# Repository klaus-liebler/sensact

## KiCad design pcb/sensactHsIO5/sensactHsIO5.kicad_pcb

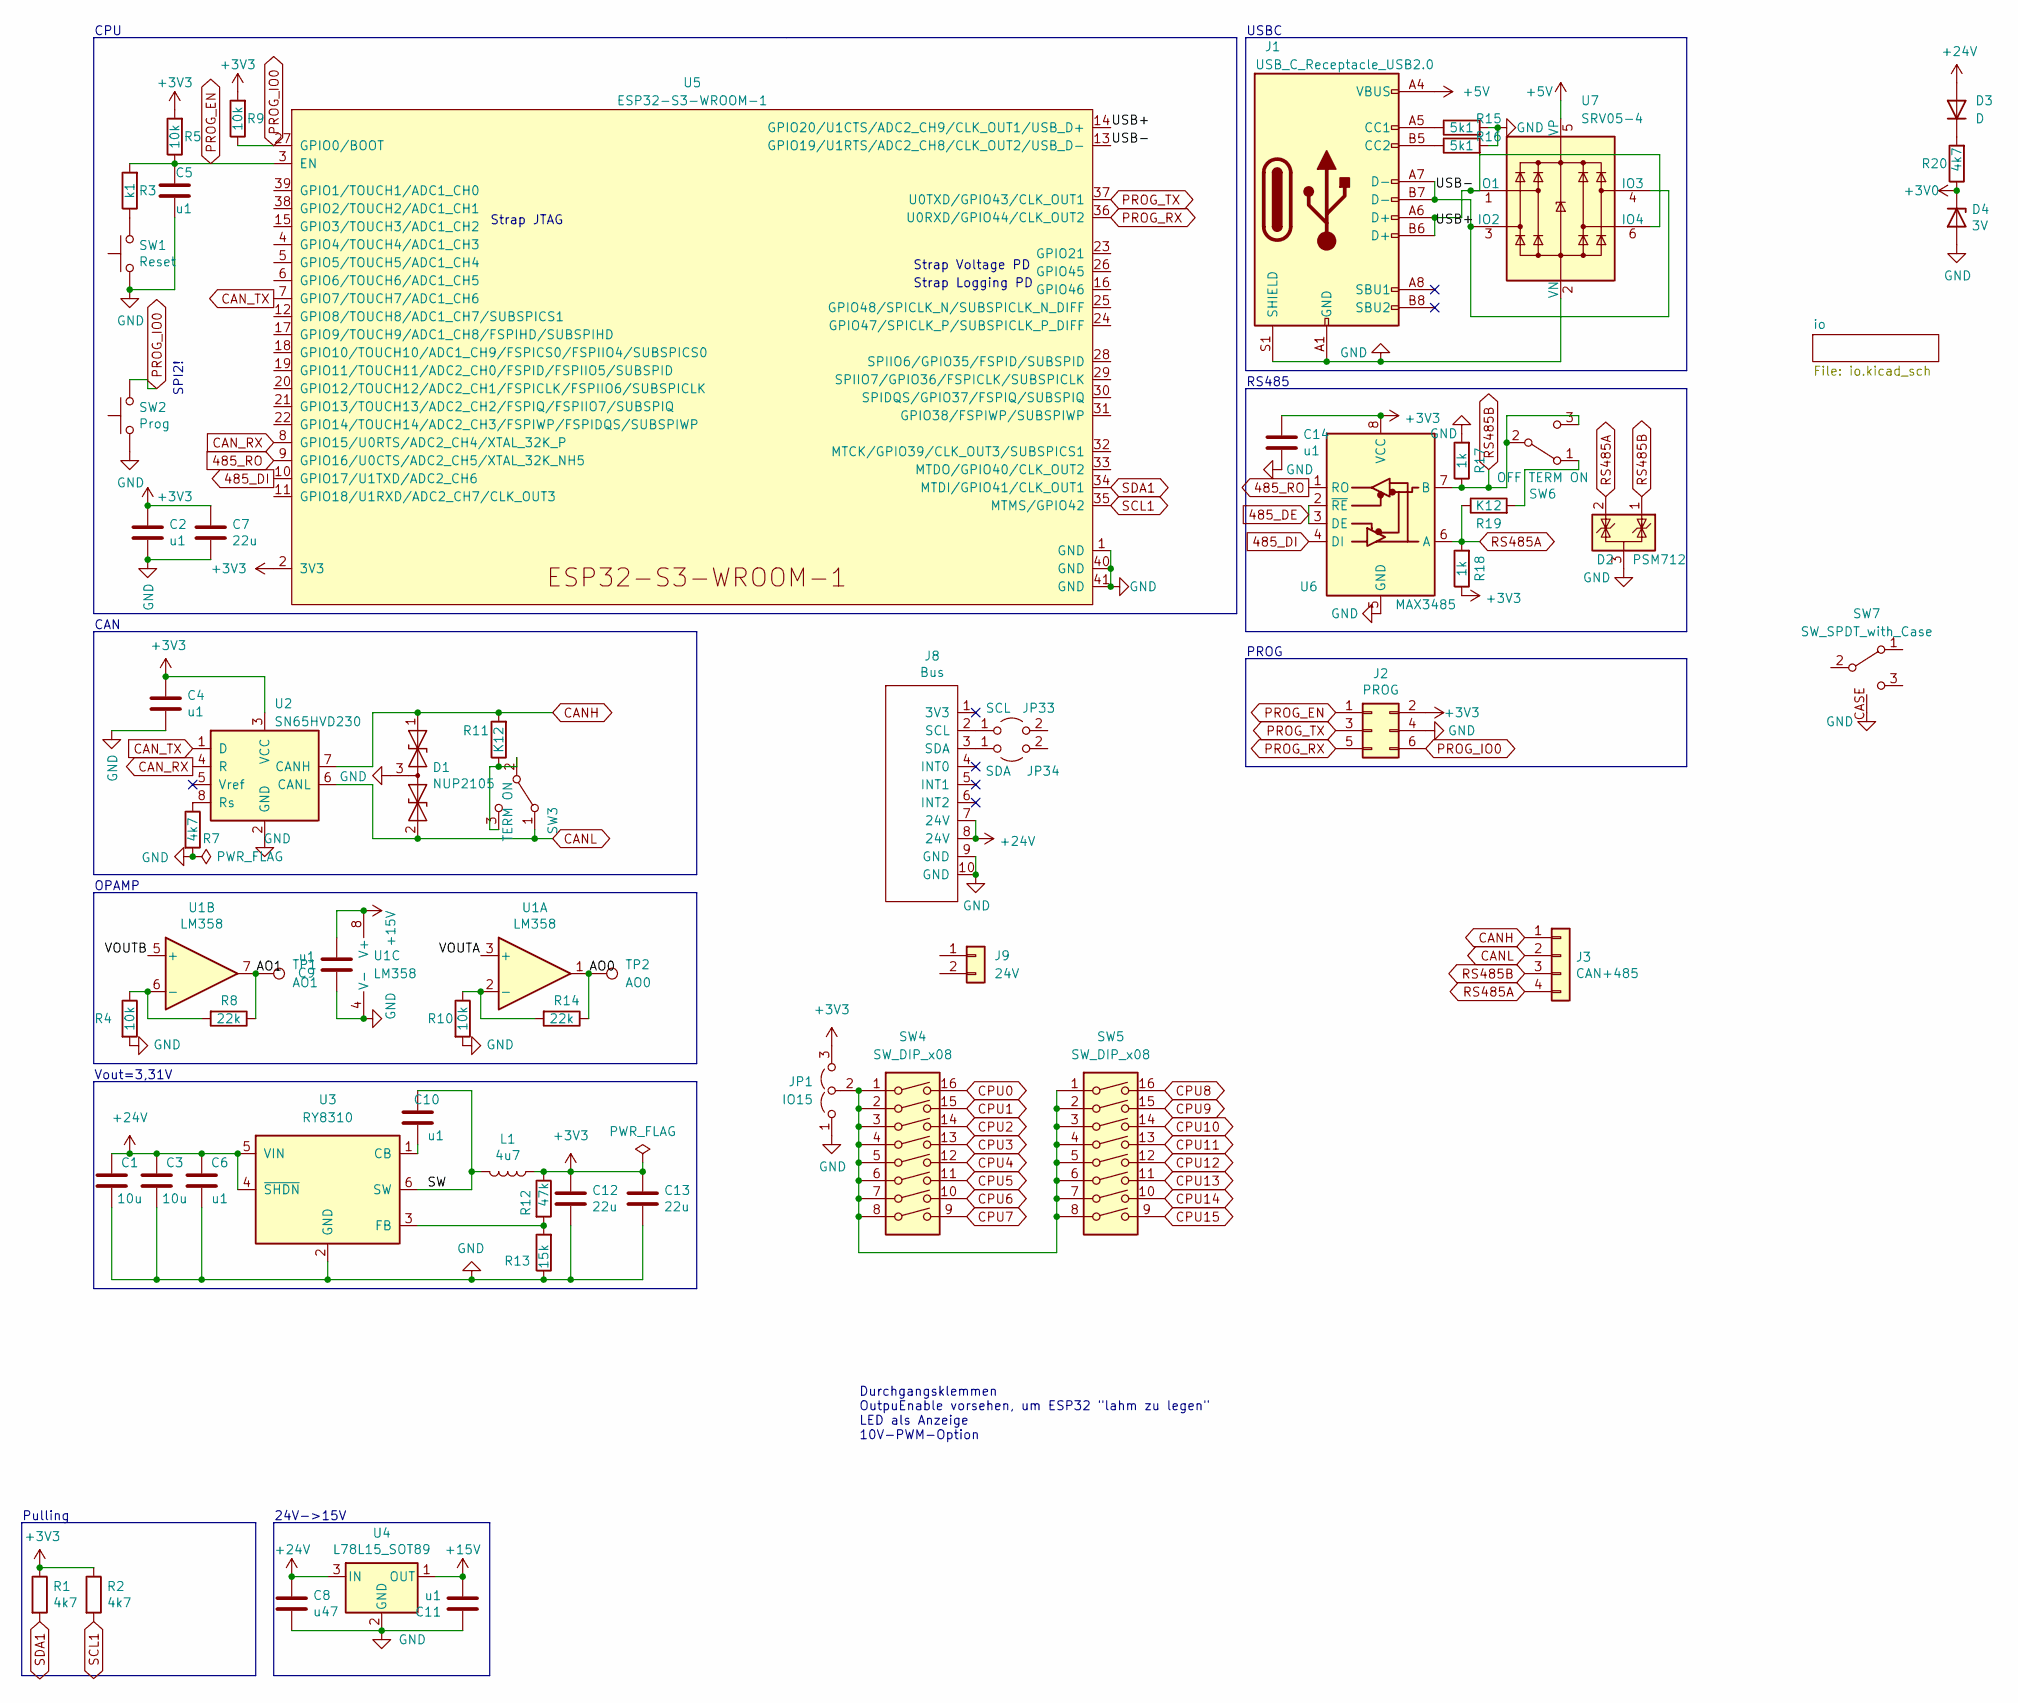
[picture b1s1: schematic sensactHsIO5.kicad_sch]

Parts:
C1, C3: 10u; C_1206_3216Metric
C2, C4, C5, C9, C11, C14: u1; C_0402_1005Metric
C6, C10: u1; C_0603_1608Metric
C7, C12, C13: 22u; C_0603_1608Metric
C8: u47; C_0805_2012Metric
D1: NUP2105; SOT-23_Handsoldering
D2: PSM712; SOT-23_Handsoldering
D3: D; D_SOD-123
D4: 3V; D_SOD-123
J1: USB_C_Receptacle_USB2.0; USB_C_Receptacle_HRO_TYPE-C-31-M-12_smaller
J2: PROG; IDC_2x03_P1.27mm_Vertical
J3: CAN+485; PhoenixContact_MC_1,5_4-G-3.5_1x04_P3.50mm_Horizontal_small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
J8: Bus; IDC-Header_2x05_P2.54mm_Horizontal_tightCrtYd
J9: 24V; PhoenixContact_MC_1,5_2-G-3.5_1x02_P3.50mm_Horizontal
JP1: IO15; SolderJumper-3_P1.3mm_Open_RoundedPad1.0x1.5mm_smaller
JP33: SCL; SolderJumper-2_P1.3mm_Bridged2Bar_RoundedPad1.0x1.5mm
JP34: SDA; SolderJumper-2_P1.3mm_Bridged2Bar_RoundedPad1.0x1.5mm
L1: 4u7; L_Abracon_ASPI-0630LR
R1, R2, R7: 4k7; R_0402_1005Metric
R3: k1; R_0402_1005Metric
R4, R5, R9, R10: 10k; R_0402_1005Metric
R8, R14: 22k; R_0402_1005Metric
R11, R19: K12; R_1206_3216Metric_Pad1.30x1.75mm_HandSolder
R12: 47k; R_0402_1005Metric
R13: 15k; R_0402_1005Metric
R15, R16: 5k1; R_0402_1005Metric
R17, R18: 1k; R_0603_1608Metric
R20: 4k7; R_1206_3216Metric
SW1: Reset; Button_2x4x3,5_handsolder
SW2: Prog; Button_2x4x3,5_handsolder
SW3: TERM ON; SW_SPDT_PCM12_handsolder
SW4, SW5: SW_DIP_x08; SW_DIP_SPSTx08_Piano
SW6: OFF TERM ON; SW_SPDT_PCM12_handsolder
SW7: SW_SPDT_with_Case; SW_SPDT_PCM12_handsolder
TP1: AO1; TestPoint_Pad_2.0x2.0mm
TP2: AO0; TestPoint_Pad_2.0x2.0mm
U1: LM358; SOIC-8_3.9x4.9mm_P1.27mm
U2: SN65HVD230; SOIC-8_3.9x4.9mm_P1.27mm
U3: RY8310; SOT-23-6
U4: L78L15_SOT89; SOT-89-3_Handsoldering
U5: ESP32-S3-WROOM-1; ESP32-S3-WROOM-1U
U6: MAX3485; SOIC-8_3.9x4.9mm_P1.27mm
U7: SRV05-4; SOT-23-6

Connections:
485_DE: U6.2 (~RE), U6.3 (DE)
485_DI: U5.10 (GPIO17/U1TXD/ADC2_CH6), U6.4 (DI)
485_RO: U5.9 (GPIO16/U0CTS/ADC2_CH5/XTAL_32K_NH5), U6.1 (RO)
+3V0: D4.1 (K), R20.1; also elsewhere on the board
+3V3: C2.1, C4.1, C7.1, C12.1, C13.1, C14.2, J2.2, JP1.3 (B), L1.1, R1.1, R2.1, R5.2, R9.2, R12.1, R18.1, U2.3 (VCC), U5.2 (3V3), U6.8 (VCC); also elsewhere on the board
+5V: J1.A4 (VBUS), J1.A9 (VBUS), J1.B4 (VBUS), J1.B9 (VBUS), U7.5 (VP)
+15V: C9.2, C11.2, U1.8 (V+), U4.1 (OUT)
+24V: C1.2, C3.2, C6.2, C8.1, D3.2 (A), J8.7 (24V), J8.8 (24V), U3.4 (~SHDN), U3.5 (VIN), U4.3 (IN); also elsewhere on the board
/AO0: R14.1, TP2.1, U1.1
/AO1: R8.1, TP1.1, U1.7
/SW: C10.2, L1.2, U3.6 (SW)
/USB+: J1.A6 (D+), J1.B6 (D+), U5.14 (GPIO20/U1CTS/ADC2_CH9/CLK_OUT1/USB_D+), U7.1 (IO1), U7.6 (IO4)
/USB-: J1.A7 (D-), J1.B7 (D-), U5.13 (GPIO19/U1RTS/ADC2_CH8/CLK_OUT2/USB_D-), U7.3 (IO2), U7.4 (IO3)
/VOUTA: U1.3 (+)
/VOUTB: U1.5 (+)
CANH: D1.1 (A1), J3.1, R11.2, U2.7 (CANH)
CANL: D1.2 (A2), J3.2, SW3.1 (A), U2.6 (CANL)
CAN_RX: U2.4 (R), U5.8 (GPIO15/U0RTS/ADC2_CH4/XTAL_32K_P)
CAN_TX: U2.1 (D), U5.7 (GPIO7/TOUCH7/ADC1_CH6)
CPU0: SW4.16; also elsewhere on the board
CPU1: SW4.15; also elsewhere on the board
CPU2: SW4.14; also elsewhere on the board
CPU3: SW4.13; also elsewhere on the board
CPU4: SW4.12; also elsewhere on the board
CPU5: SW4.11; also elsewhere on the board
CPU6: SW4.10; also elsewhere on the board
CPU7: SW4.9; also elsewhere on the board
CPU8: SW5.16; also elsewhere on the board
CPU9: SW5.15; also elsewhere on the board
CPU10: SW5.14; also elsewhere on the board
CPU11: SW5.13; also elsewhere on the board
CPU12: SW5.12; also elsewhere on the board
CPU13: SW5.11; also elsewhere on the board
CPU14: SW5.10; also elsewhere on the board
CPU15: SW5.9; also elsewhere on the board
GND: C1.1, C2.2, C3.1, C4.2, C5.2, C6.1, C7.2, C8.2, C9.1, C11.1, C12.2, C13.2, C14.1, D1.3 (common), D2.3 (A), D4.2 (A), J1.A1 (GND), J1.A12 (GND), J1.B1 (GND), J1.B12 (GND), J1.S1 (SHIELD), J2.4, J8.9 (GND), J8.10 (GND), JP1.1 (A), R4.2, R7.2, R10.2, R13.1, R15.2, R16.2, R17.2, SW1.1, SW2.1, SW7.CASE, U1.4 (V-), U2.2 (GND), U3.2 (GND), U4.2 (GND), U5.1 (GND), U5.40 (GND), U5.41 (GND), U6.5 (GND), U7.2 (VN); also elsewhere on the board
unnamed: C10.1, U3.1 (CB)
unnamed: D3.1 (K), R20.2
unnamed: J1.A5 (CC1), R15.1
unnamed: J1.B5 (CC2), R16.1
unnamed: J8.2 (SCL), JP33.1 (A)
unnamed: J8.3 (SDA), JP34.1 (A)
unnamed: JP1.2 (C), SW4.1, SW4.2, SW4.3, SW4.4, SW4.5, SW4.6, SW4.7, SW4.8, SW5.1, SW5.2, SW5.3, SW5.4, SW5.5, SW5.6, SW5.7, SW5.8
unnamed: R3.1, SW1.2
unnamed: R4.1, R8.2, U1.6 (-)
unnamed: R7.1, U2.8 (Rs)
unnamed: R10.1, R14.2, U1.2 (-)
unnamed: R12.2, R13.2, U3.3 (FB)
unnamed: R19.2, SW6.1 (A)
unnamed: R11.1, SW3.2 (B), SW3.3 (C)
PROG_EN: C5.1, J2.1, R3.2, R5.1, U5.3 (EN)
PROG_IO0: J2.6, R9.1, SW2.2, U5.27 (GPIO0/BOOT)
PROG_RX: J2.5, U5.36 (U0RXD/GPIO44/CLK_OUT2)
PROG_TX: J2.3, U5.37 (U0TXD/GPIO43/CLK_OUT1)
RS485A: D2.2 (K), J3.4, R18.2, R19.1, U6.6 (A)
RS485B: D2.1 (K), J3.3, R17.1, SW6.2 (B), SW6.3 (C), U6.7 (B)
SCL1: R2.2, U5.35 (MTMS/GPIO42)
SDA1: R1.2, U5.34 (MTDI/GPIO41/CLK_OUT1)

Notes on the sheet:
SPI2!
USBC
Strap JTAG
Vout=3,31V
Strap Logging PD
Pulling
PROG
RS485
Durchgangsklemmen OutpuEnable vorsehen, um ESP32 "lahm zu legen" LED als Anzeige 10V-PWM-Option
Strap Voltage PD
OPAMP
CAN
24V->15V
CPU

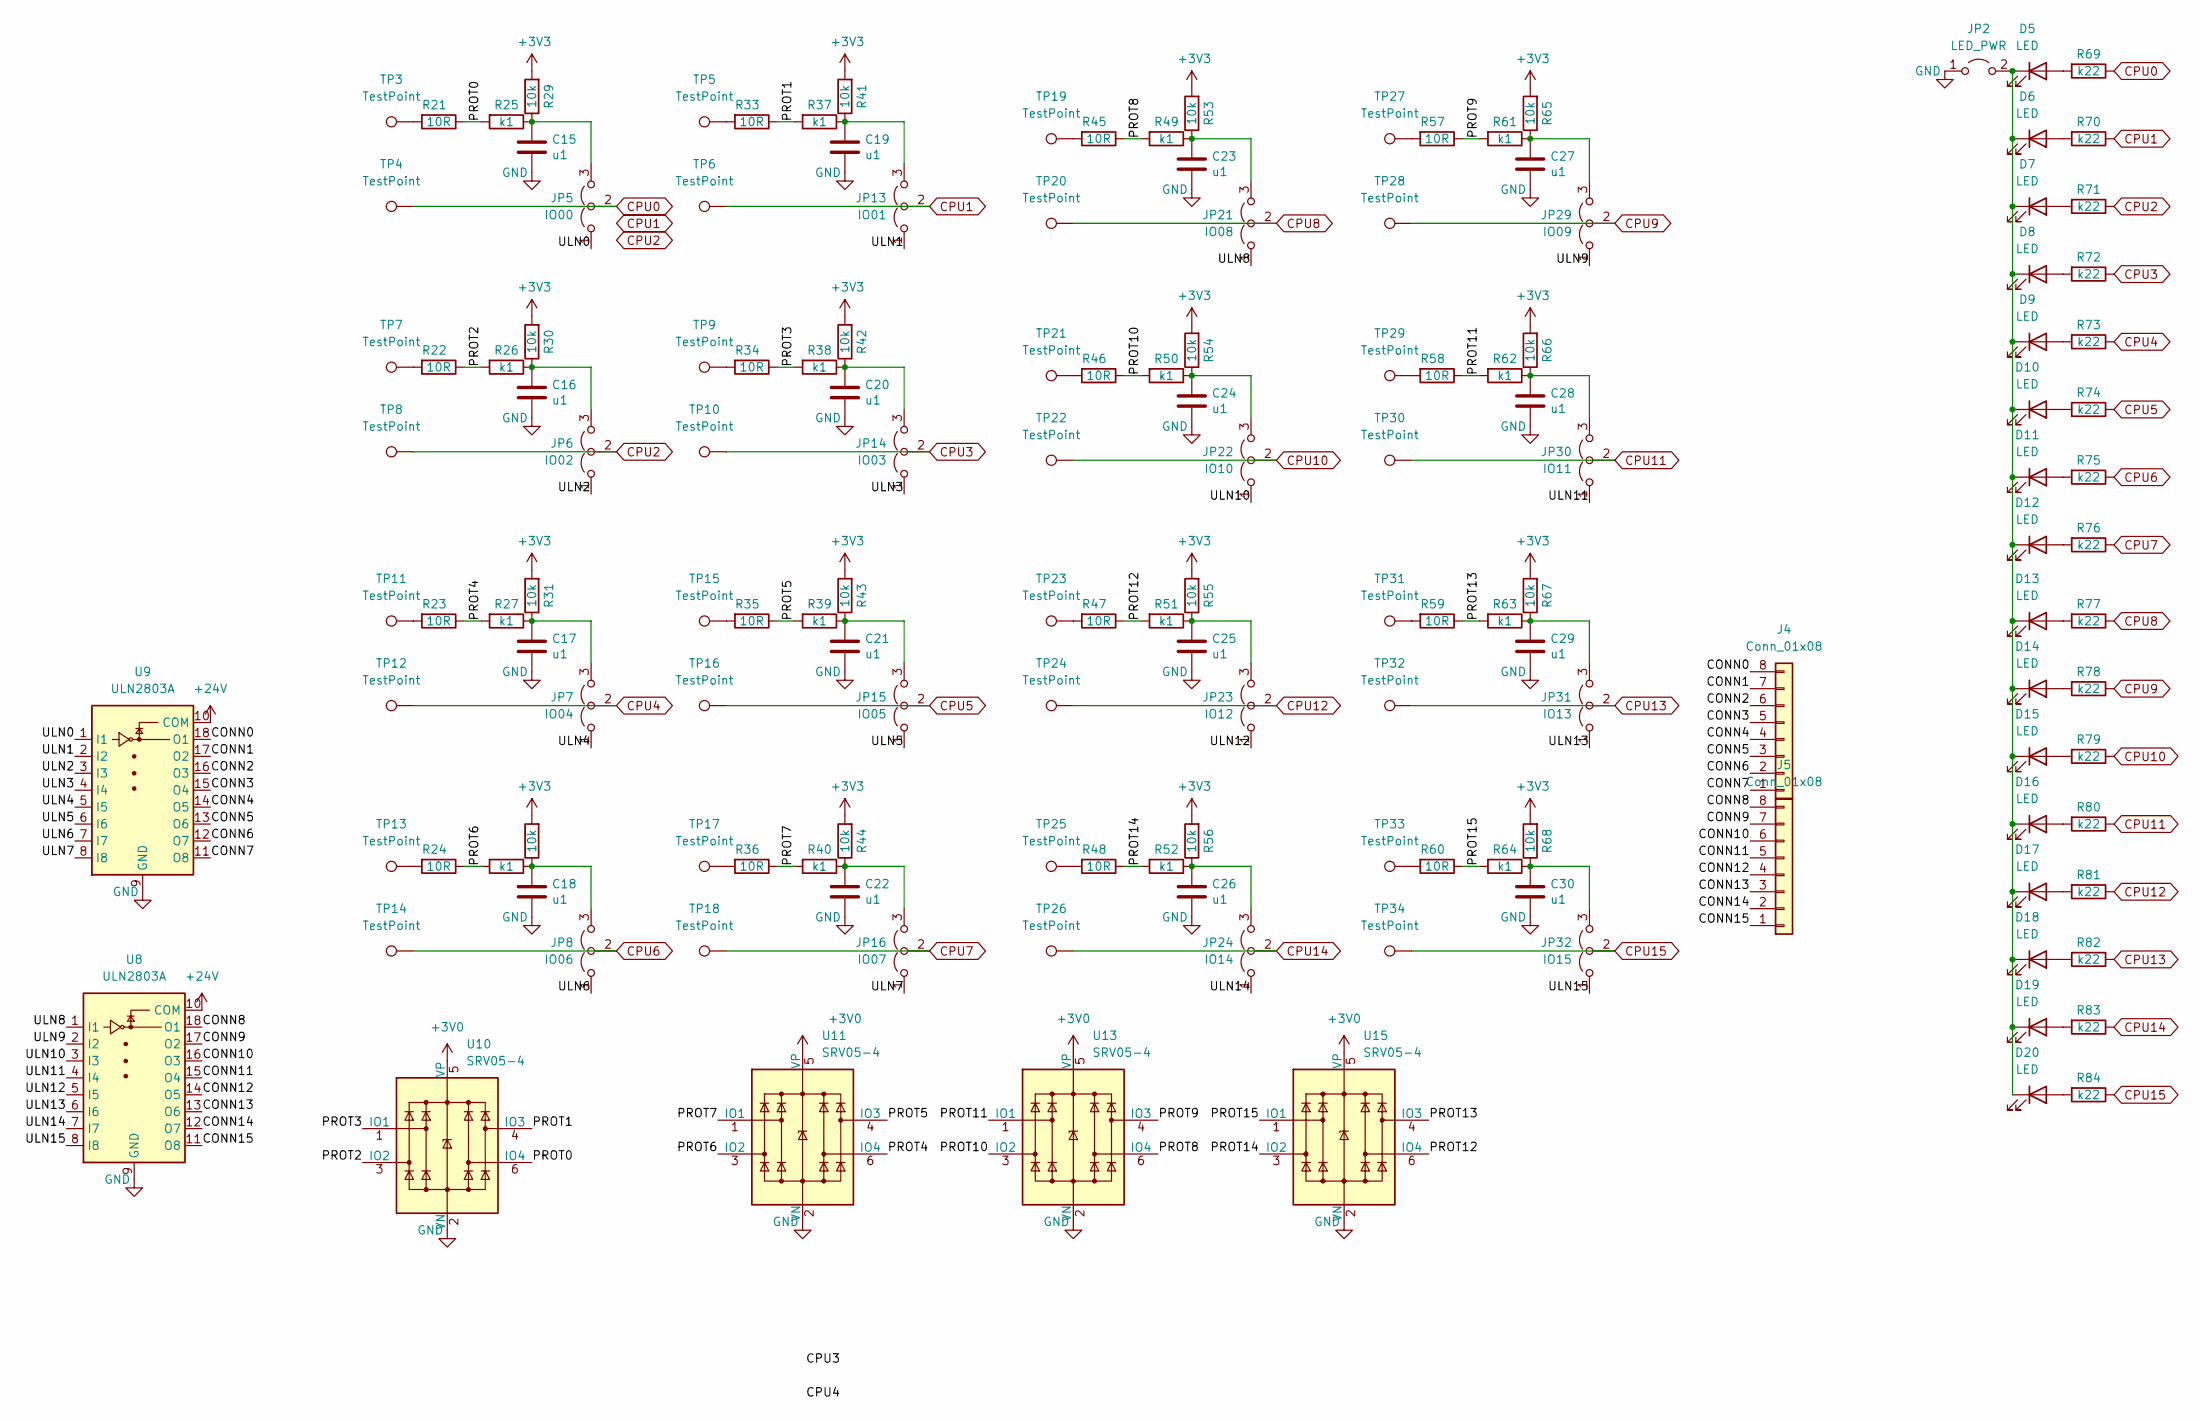
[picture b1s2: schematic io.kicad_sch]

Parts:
C15, C16, C17, C18, C19, C20, C21, C22, C23, C24, C25, C26, C27, C28, C29, C30: u1; C_0402_1005Metric
D5, D6, D7, D8, D9, D10, D11, D12, D13, D14, D15, D16, D17, D18, D19, D20: LED; LED_1606
J4, J5: Conn_01x08; KF141R-8p
JP2: LED_PWR; SolderJumper-2_P1.3mm_Open_RoundedPad1.0x1.5mm
JP5: IO00; SolderJumper-3_P1.3mm_Open_RoundedPad1.0x1.5mm_smaller
JP6: IO02; SolderJumper-3_P1.3mm_Open_RoundedPad1.0x1.5mm_smaller
JP7: IO04; SolderJumper-3_P1.3mm_Open_RoundedPad1.0x1.5mm_smaller
JP8: IO06; SolderJumper-3_P1.3mm_Open_RoundedPad1.0x1.5mm_smaller
JP13: IO01; SolderJumper-3_P1.3mm_Open_RoundedPad1.0x1.5mm_smaller
JP14: IO03; SolderJumper-3_P1.3mm_Open_RoundedPad1.0x1.5mm_smaller
JP15: IO05; SolderJumper-3_P1.3mm_Open_RoundedPad1.0x1.5mm_smaller
JP16: IO07; SolderJumper-3_P1.3mm_Open_RoundedPad1.0x1.5mm_smaller
JP21: IO08; SolderJumper-3_P1.3mm_Open_RoundedPad1.0x1.5mm_smaller
JP22: IO10; SolderJumper-3_P1.3mm_Open_RoundedPad1.0x1.5mm_smaller
JP23: IO12; SolderJumper-3_P1.3mm_Open_RoundedPad1.0x1.5mm_smaller
JP24: IO14; SolderJumper-3_P1.3mm_Open_RoundedPad1.0x1.5mm_smaller
JP29: IO09; SolderJumper-3_P1.3mm_Open_RoundedPad1.0x1.5mm_smaller
JP30: IO11; SolderJumper-3_P1.3mm_Open_RoundedPad1.0x1.5mm_smaller
JP31: IO13; SolderJumper-3_P1.3mm_Open_RoundedPad1.0x1.5mm_smaller
JP32: IO15; SolderJumper-3_P1.3mm_Open_RoundedPad1.0x1.5mm_smaller
R21, R22, R23, R24, R33, R34, R35, R36, R45, R46, R47, R48, R57, R58, R59, R60: 10R; R_0402_1005Metric
R25, R26, R27, R28, R37, R38, R39, R40, R49, R50, R51, R52, R61, R62, R63, R64: k1; R_0402_1005Metric
R29, R30, R31, R32, R41, R42, R43, R44, R53, R54, R55, R56, R65, R66, R67, R68: 10k; R_0402_1005Metric
R69, R70, R71, R72, R73, R74, R75, R76, R77, R78, R79, R80, R81, R82, R83, R84: k22; R_0402_1005Metric
TP3, TP4, TP5, TP6, TP7, TP8, TP9, TP10, TP11, TP12, TP13, TP14, TP15, TP16, TP17, TP18, TP19, TP20, TP21, TP22, TP23, TP24, TP25, TP26, TP27, TP28, TP29, TP30, TP31, TP32, TP33, TP34: TestPoint; SolderJumper-3_forMCConnector
U8, U9: ULN2803A; SOIC-18W_7.5x11.6mm_P1.27mm
U10, U11, U13, U15: SRV05-4; SOT-23-6-spezial

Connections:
+3V0: U10.5 (VP), U11.5 (VP), U13.5 (VP), U15.5 (VP); also elsewhere on the board
+3V3: R29.2, R30.2, R31.2, R32.2, R41.2, R42.2, R43.2, R44.2, R53.2, R54.2, R55.2, R56.2, R65.2, R66.2, R67.2, R68.2; also elsewhere on the board
+24V: U8.10 (COM), U9.10 (COM); also elsewhere on the board
/io/CONN0: J4.8, U9.18 (O1)
/io/CONN1: J4.7, U9.17 (O2)
/io/CONN2: J4.6, U9.16 (O3)
/io/CONN3: J4.5, U9.15 (O4)
/io/CONN4: J4.4, U9.14 (O5)
/io/CONN5: J4.3, U9.13 (O6)
/io/CONN6: J4.2, U9.12 (O7)
/io/CONN7: J4.1, U9.11 (O8)
/io/CONN8: J5.8, U8.18 (O1)
/io/CONN9: J5.7, U8.17 (O2)
/io/CONN10: J5.6, U8.16 (O3)
/io/CONN11: J5.5, U8.15 (O4)
/io/CONN12: J5.4, U8.14 (O5)
/io/CONN13: J5.3, U8.13 (O6)
/io/CONN14: J5.2, U8.12 (O7)
/io/CONN15: J5.1, U8.11 (O8)
/io/PROT0: R21.1, R25.2, U10.6 (IO4)
/io/PROT1: R33.1, R37.2, U10.4 (IO3)
/io/PROT2: R22.1, R26.2, U10.3 (IO2)
/io/PROT3: R34.1, R38.2, U10.1 (IO1)
/io/PROT4: R23.1, R27.2, U11.6 (IO4)
/io/PROT5: R35.1, R39.2, U11.4 (IO3)
/io/PROT6: R24.1, R28.2, U11.3 (IO2)
/io/PROT7: R36.1, R40.2, U11.1 (IO1)
/io/PROT8: R45.1, R49.2, U13.6 (IO4)
/io/PROT9: R57.1, R61.2, U13.4 (IO3)
/io/PROT10: R46.1, R50.2, U13.3 (IO2)
/io/PROT11: R58.1, R62.2, U13.1 (IO1)
/io/PROT12: R47.1, R51.2, U15.6 (IO4)
/io/PROT13: R59.1, R63.2, U15.4 (IO3)
/io/PROT14: R48.1, R52.2, U15.3 (IO2)
/io/PROT15: R60.1, R64.2, U15.1 (IO1)
/io/ULN0: JP5.1 (A), U9.1 (I1)
/io/ULN1: JP13.1 (A), U9.2 (I2)
/io/ULN2: JP6.1 (A), U9.3 (I3)
/io/ULN3: JP14.1 (A), U9.4 (I4)
/io/ULN4: JP7.1 (A), U9.5 (I5)
/io/ULN5: JP15.1 (A), U9.6 (I6)
/io/ULN6: JP8.1 (A), U9.7 (I7)
/io/ULN7: JP16.1 (A), U9.8 (I8)
/io/ULN8: JP21.1 (A), U8.1 (I1)
/io/ULN9: JP29.1 (A), U8.2 (I2)
/io/ULN10: JP22.1 (A), U8.3 (I3)
/io/ULN11: JP30.1 (A), U8.4 (I4)
/io/ULN12: JP23.1 (A), U8.5 (I5)
/io/ULN13: JP31.1 (A), U8.6 (I6)
/io/ULN14: JP24.1 (A), U8.7 (I7)
/io/ULN15: JP32.1 (A), U8.8 (I8)
CPU0: JP5.2 (C), R69.1, TP4.1; also elsewhere on the board
CPU1: JP13.2 (C), R70.1, TP6.1; also elsewhere on the board
CPU2: JP6.2 (C), R71.1, TP8.1; also elsewhere on the board
CPU3: JP14.2 (C), R72.1, TP10.1; also elsewhere on the board
CPU4: JP7.2 (C), R73.1, TP12.1; also elsewhere on the board
CPU5: JP15.2 (C), R74.1, TP16.1; also elsewhere on the board
CPU6: JP8.2 (C), R75.1, TP14.1; also elsewhere on the board
CPU7: JP16.2 (C), R76.1, TP18.1; also elsewhere on the board
CPU8: JP21.2 (C), R77.1, TP20.1; also elsewhere on the board
CPU9: JP29.2 (C), R78.1, TP28.1; also elsewhere on the board
CPU10: JP22.2 (C), R79.1, TP22.1; also elsewhere on the board
CPU11: JP30.2 (C), R80.1, TP30.1; also elsewhere on the board
CPU12: JP23.2 (C), R81.1, TP24.1; also elsewhere on the board
CPU13: JP31.2 (C), R82.1, TP32.1; also elsewhere on the board
CPU14: JP24.2 (C), R83.1, TP26.1; also elsewhere on the board
CPU15: JP32.2 (C), R84.1, TP34.1; also elsewhere on the board
GND: C15.2, C16.2, C17.2, C18.2, C19.2, C20.2, C21.2, C22.2, C23.2, C24.2, C25.2, C26.2, C27.2, C28.2, C29.2, C30.2, JP2.1 (A), U8.9 (GND), U9.9 (GND), U10.2 (VN), U11.2 (VN), U13.2 (VN), U15.2 (VN); also elsewhere on the board
unnamed: C15.1, JP5.3 (B), R25.1, R29.1
unnamed: C16.1, JP6.3 (B), R26.1, R30.1
unnamed: C17.1, JP7.3 (B), R27.1, R31.1
unnamed: C18.1, JP8.3 (B), R28.1, R32.1
unnamed: C19.1, JP13.3 (B), R37.1, R41.1
unnamed: C20.1, JP14.3 (B), R38.1, R42.1
unnamed: C21.1, JP15.3 (B), R39.1, R43.1
unnamed: C22.1, JP16.3 (B), R40.1, R44.1
unnamed: C23.1, JP21.3 (B), R49.1, R53.1
unnamed: C24.1, JP22.3 (B), R50.1, R54.1
unnamed: C25.1, JP23.3 (B), R51.1, R55.1
unnamed: C26.1, JP24.3 (B), R52.1, R56.1
unnamed: C27.1, JP29.3 (B), R61.1, R65.1
unnamed: C28.1, JP30.3 (B), R62.1, R66.1
unnamed: C29.1, JP31.3 (B), R63.1, R67.1
unnamed: C30.1, JP32.3 (B), R64.1, R68.1
unnamed: D5.1 (K), D6.1 (K), D7.1 (K), D8.1 (K), D9.1 (K), D10.1 (K), D11.1 (K), D12.1 (K), D13.1 (K), D14.1 (K), D15.1 (K), D16.1 (K), D17.1 (K), D18.1 (K), D19.1 (K), D20.1 (K), JP2.2 (B)
unnamed: D16.2 (A), R80.2
unnamed: R21.2, TP3.1
unnamed: R22.2, TP7.1
unnamed: R23.2, TP11.1
unnamed: R24.2, TP13.1
unnamed: R33.2, TP5.1
unnamed: R34.2, TP9.1
unnamed: R35.2, TP15.1
unnamed: R36.2, TP17.1
unnamed: R45.2, TP19.1
unnamed: R46.2, TP21.1
unnamed: R47.2, TP23.1
unnamed: R48.2, TP25.1
unnamed: R57.2, TP27.1
unnamed: R58.2, TP29.1
unnamed: R59.2, TP31.1
unnamed: R60.2, TP33.1
unnamed: D5.2 (A), R69.2
unnamed: D6.2 (A), R70.2
unnamed: D7.2 (A), R71.2
unnamed: D8.2 (A), R72.2
unnamed: D9.2 (A), R73.2
unnamed: D10.2 (A), R74.2
unnamed: D11.2 (A), R75.2
unnamed: D12.2 (A), R76.2
unnamed: D13.2 (A), R77.2
unnamed: D14.2 (A), R78.2
unnamed: D15.2 (A), R79.2
unnamed: D17.2 (A), R81.2
unnamed: D18.2 (A), R82.2
unnamed: D19.2 (A), R83.2
unnamed: D20.2 (A), R84.2

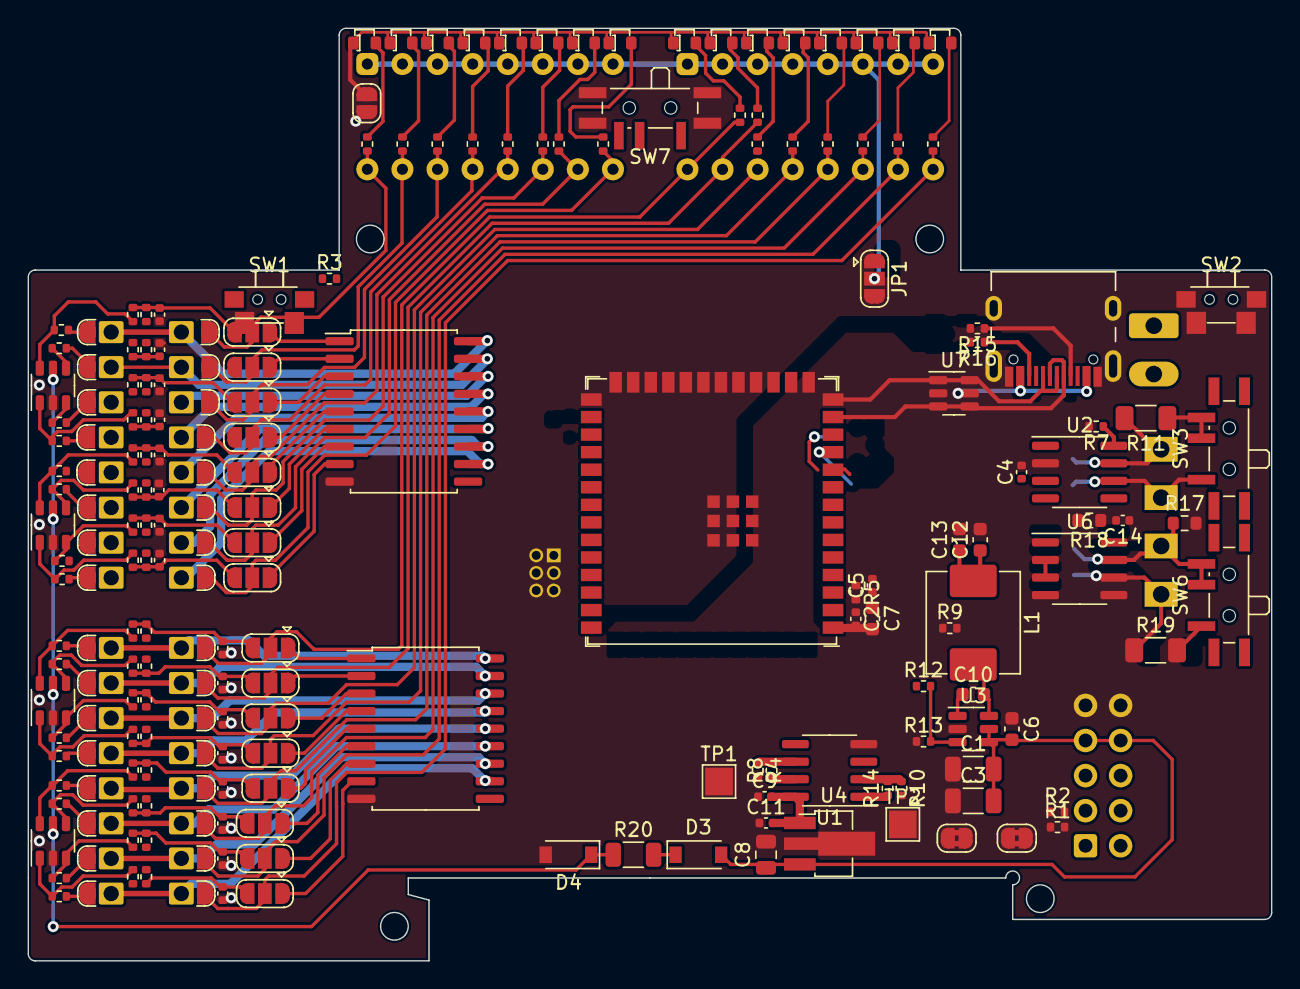
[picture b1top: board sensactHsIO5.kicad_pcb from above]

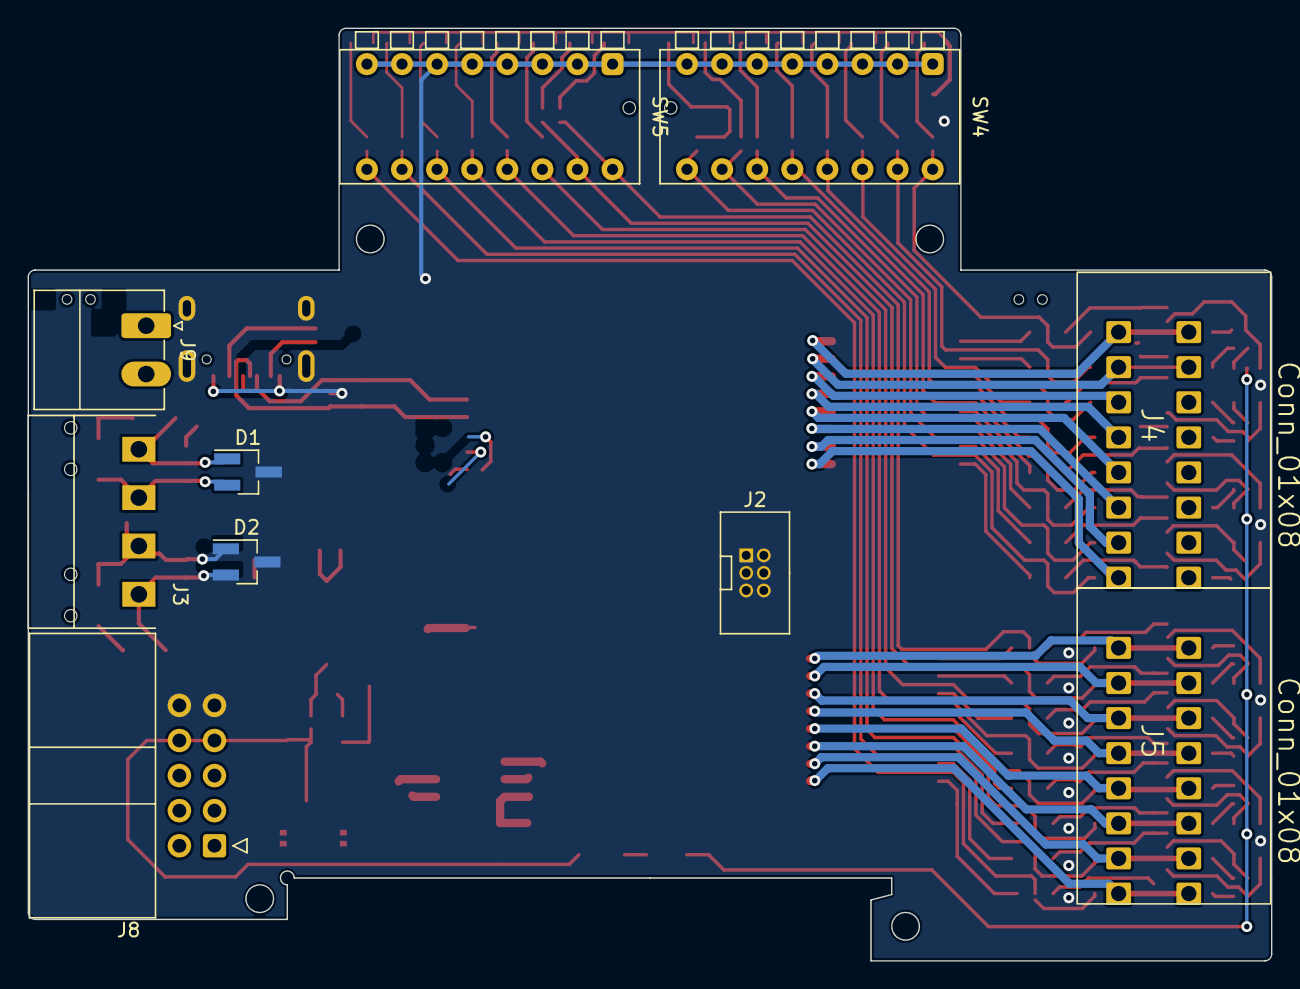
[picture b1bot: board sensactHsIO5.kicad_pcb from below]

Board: 2 copper layers, 90.0 x 67.5 mm, 215 parts (10 on the bottom side), 153 nets.

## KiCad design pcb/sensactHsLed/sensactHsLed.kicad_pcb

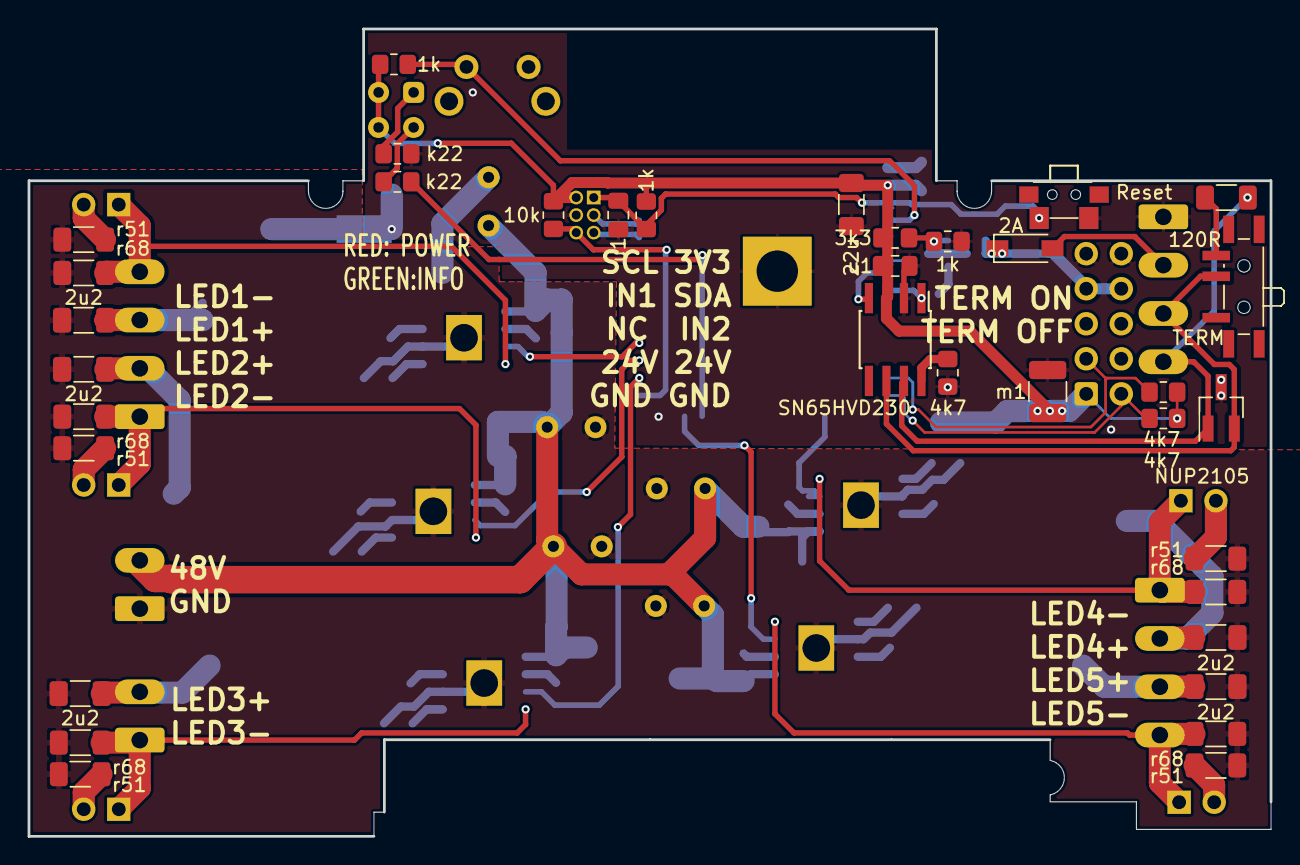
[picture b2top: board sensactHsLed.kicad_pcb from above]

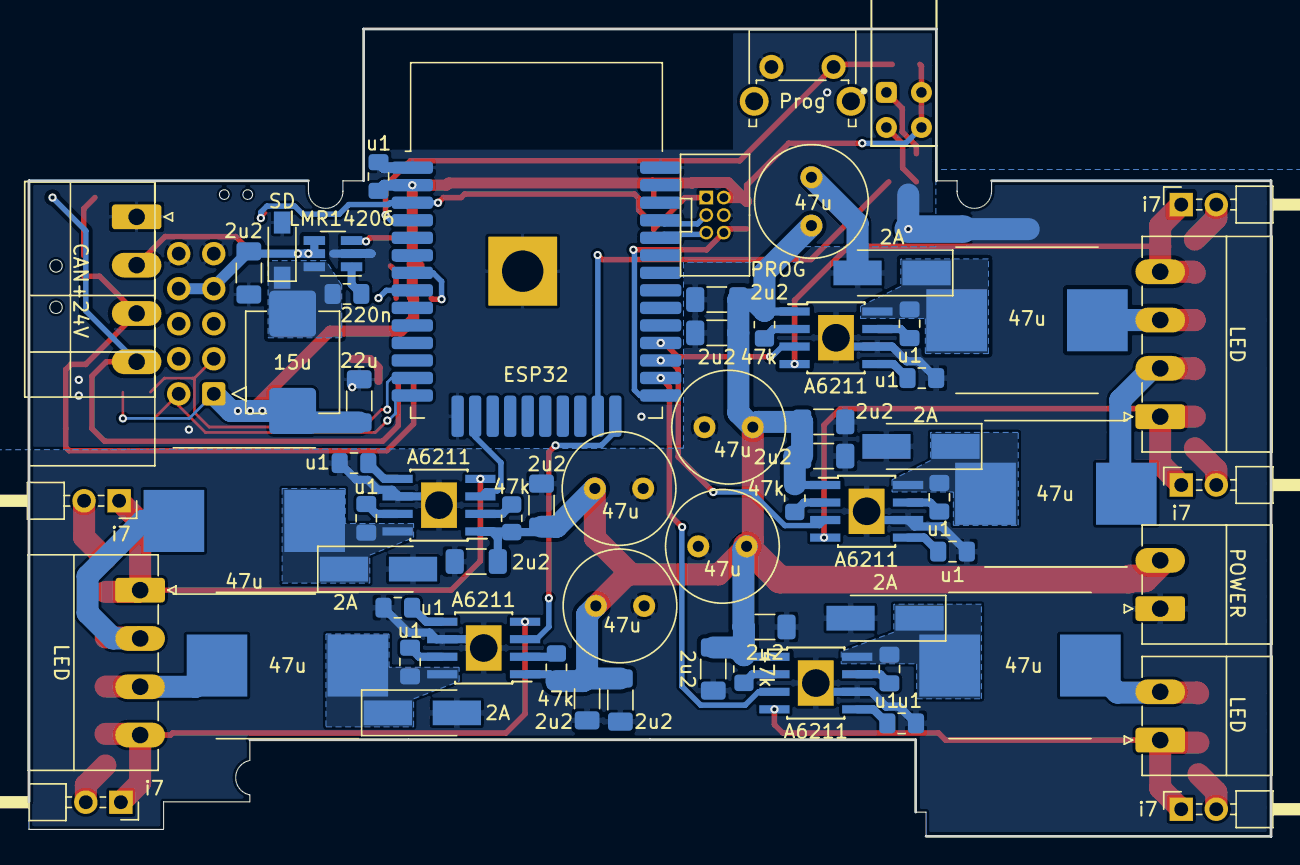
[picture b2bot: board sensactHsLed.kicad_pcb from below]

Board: 2 copper layers, 90.0 x 58.5 mm, 103 parts (68 on the bottom side), 65 nets.

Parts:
C1, C7, C13, C19, C26: 47u; C_Radial_D8.0mm_H11.5mm_P3.50mm
C2, C3, C6, C8, C9, C12, C14, C15, C18, C20, C21, C25, C27, C28, C31, C34: 2u2; C_1206_3216Metric_Pad1.33x1.80mm_HandSolder
C4, C5, C10, C11, C16, C17, C22, C23, C24, C29, C30, C32, C40: u1; C_0805_2012Metric_Pad1.18x1.45mm_HandSolder
C33, C36: 22u; C_1206_3216Metric_Pad1.33x1.80mm_HandSolder
C35: 220n; C_0805_2012Metric_Pad1.18x1.45mm_HandSolder
C37: m1; C_1210_3225Metric_Pad1.33x2.70mm_HandSolder
D1: Rpower_Ginfo; Dialight-5530123F-0
D2: SD; D_SOD-123_handsolder
D3: NUP2105; SOT-23_Handsoldering
D4: 2A; D_SOD-123_handsolder
D5, D6, D7, D8, D9: 2A; D_SMA_Handsoldering
J1: PROG; IDC_2x03_P1.27mm_Vertical
J2: SensactBusConnector; IDC-Header_2x05_P2.54mm_Horizontal
J3: CAN+24V; PhoenixContact_MC_1,5_4-G-3.5_1x04_P3.50mm_Horizontal
J4, J7: LED; PhoenixContact_MC_1,5_4-G-3.5_1x04_P3.50mm_Horizontal
J5: LED; PhoenixContact_MC_1,5_2-G-3.5_1x02_P3.50mm_Horizontal
J6: POWER; PhoenixContact_MC_1,5_2-G-3.5_1x02_P3.50mm_Horizontal
JP2, JP4, JP6, JP8, JP10: i7; PinHeader_2x01_P2.54mm_Horizontal
L1, L2, L3, L4, L6: 47u; L_1040
L5: 15u; L_0630
NT1: Net-Tie_2; NetTie-2_SMD_Pad2.0mm
R1, R3, R6: 4k7; R_0805_2012Metric_Pad1.20x1.40mm_HandSolder
R2, R8, R12, R16, R19: 47k; R_0805_2012Metric_Pad1.20x1.40mm_HandSolder
R4, R9, R14, R17, R20: r68; R_1206_3216Metric_Pad1.30x1.75mm_HandSolder
R5, R10, R15, R18, R21: r51; R_1206_3216Metric_Pad1.30x1.75mm_HandSolder
R7: 120R; R_1206_3216Metric_Pad1.30x1.75mm_HandSolder
R11, R13, R23: 1k; R_0805_2012Metric_Pad1.20x1.40mm_HandSolder
R22: 3k3; R_0805_2012Metric_Pad1.20x1.40mm_HandSolder
R25: 10k; R_0805_2012Metric_Pad1.20x1.40mm_HandSolder
R26, R27: k22; R_0805_2012Metric_Pad1.20x1.40mm_HandSolder
SW1: TERM; SW_SPDT_PCM12_handsolder
SW2: Prog; SW_Tactile_SPST_Angled_PTS645Vx58-2LFS
SW3: Reset; SW_SPST_2x4x3,5
U1, U2, U4, U6, U8: A6211; SOIC-8_3.9x4.9mm_Pitch1.27mm_pad_handsolder
U3: ESP32; ESP32-WROOM-32_HANDSOLDER
U5: SN65HVD230; SOIC-8_3.9x4.9mm_Pitch1.27mm_handsolder
U7: LMR14206; SOT-23-6_Handsoldering

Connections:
+3V3: C22.1, C32.1, C33.1, C36.1, C37.1, D1.2, D1.4, J1.2, J2.1, L5.1, R1.1, R6.1, R11.1, R13.1, R22.1, R25.1, U3.2, U5.3
+24V: C34.1, D4.1, J2.7, J2.8, U7.4, U7.5
+48V: C1.1, C2.1, C3.1, C7.1, C8.1, C9.1, C13.1, C14.1, C15.1, C19.1, C20.1, C21.1, C26.1, C27.1, C28.1, J6.2, R2.2, R8.2, R12.2, R16.2, R19.2, U1.1, U2.1, U4.1, U6.1, U8.1
/ledcc01/LED+: C6.1, J4.3, L1.1
/ledcc01/LED-: J4.4, JP2.1, R4.1, U1.4
/ledcc01/SW: C5.1, D5.1, L1.2, U1.8
/ledcc2/LED+: C12.1, J4.2, L2.1
/ledcc2/LED-: J4.1, JP4.1, R9.1, U2.4
/ledcc2/SW: C11.1, D6.1, L2.2, U2.8
/ledcc3/LED+: C18.1, J5.2, L3.1
/ledcc3/LED-: J5.1, JP6.1, R14.1, U4.4
/ledcc3/SW: C17.1, D7.1, L3.2, U4.8
/ledcc4/LED+: C25.1, J7.2, L4.1
/ledcc4/LED-: J7.1, JP8.1, R17.1, U6.4
/ledcc4/SW: C24.1, D8.1, L4.2, U6.8
/ledcc5/LED+: C31.1, J7.3, L6.1
/ledcc5/LED-: J7.4, JP10.1, R20.1, U8.4
/ledcc5/SW: C30.1, D9.1, L6.2, U8.8
/psu1/SW: C35.1, D2.1, L5.2, U7.6
CANH: D3.1, J3.4, R7.2, U5.7
CANL: D3.2, J3.3, SW1.2, U5.6
CAN_RX: U3.7, U5.4
CAN_TX: U3.8, U5.1
EN: C40.1, J1.1, R11.2, SW3.1, U3.3
EN1: U1.3, U3.28
EN2: U2.3, U3.27
EN3: U3.26, U4.3
EN4: U3.16, U6.3
EN5: U3.24, U8.3
GND: C22.2, C32.2, C33.2, C34.2, C36.2, C37.2, C40.2, D2.2, D3.3, J1.4, J2.9, J2.10, J3.1, NT1.1, R3.2, R23.2, R27.2, SW2.1, SW3.2, U3.1, U3.15, U3.38, U3.39, U5.2, U7.2
GND1: C1.2, C2.2, C3.2, C4.2, C6.2, C7.2, C8.2, C9.2, C10.2, C12.2, C13.2, C14.2, C15.2, C16.2, C18.2, C19.2, C20.2, C21.2, C23.2, C25.2, C26.2, C27.2, C28.2, C29.2, C31.2, D5.2, D6.2, D7.2, D8.2, D9.2, J6.1, NT1.2, R4.2, R5.2, R9.2, R10.2, R14.2, R15.2, R17.2, R18.2, R20.2, R21.2, U1.6, U1.9, U2.6, U2.9, U4.6, U4.9, U6.6, U6.9, U8.6, U8.9
unnamed: C4.1, U1.5
unnamed: C5.2, U1.7
unnamed: C10.1, U2.5
unnamed: C11.2, U2.7
unnamed: C16.1, U4.5
unnamed: C17.2, U4.7
unnamed: C23.1, U6.5
unnamed: C24.2, U6.7
unnamed: C29.1, U8.5
unnamed: C30.2, U8.7
unnamed: C35.2, U7.1
unnamed: D1.1, R27.1
unnamed: D1.3, R26.1
unnamed: D4.2, J3.2
unnamed: JP2.2, R5.1
unnamed: JP4.2, R10.1
unnamed: JP6.2, R15.1
unnamed: JP8.2, R18.1
unnamed: JP10.2, R21.1
unnamed: R2.1, U1.2
unnamed: R3.1, U5.8
unnamed: R7.1, SW1.3
unnamed: R8.1, U2.2
unnamed: R12.1, U4.2
unnamed: R13.2, SW2.2, U3.4
unnamed: R16.1, U6.2
unnamed: R19.1, U8.2
unnamed: R22.2, R23.1, U7.3
unnamed: R26.2, U3.23
PROG_IO0: J1.6, R25.2, U3.25
PROG_RX: J1.5, U3.34
PROG_TX: J1.3, U3.35
SCL1: J2.2, R6.2, U3.14
SDA1: J2.3, R1.2, U3.13
